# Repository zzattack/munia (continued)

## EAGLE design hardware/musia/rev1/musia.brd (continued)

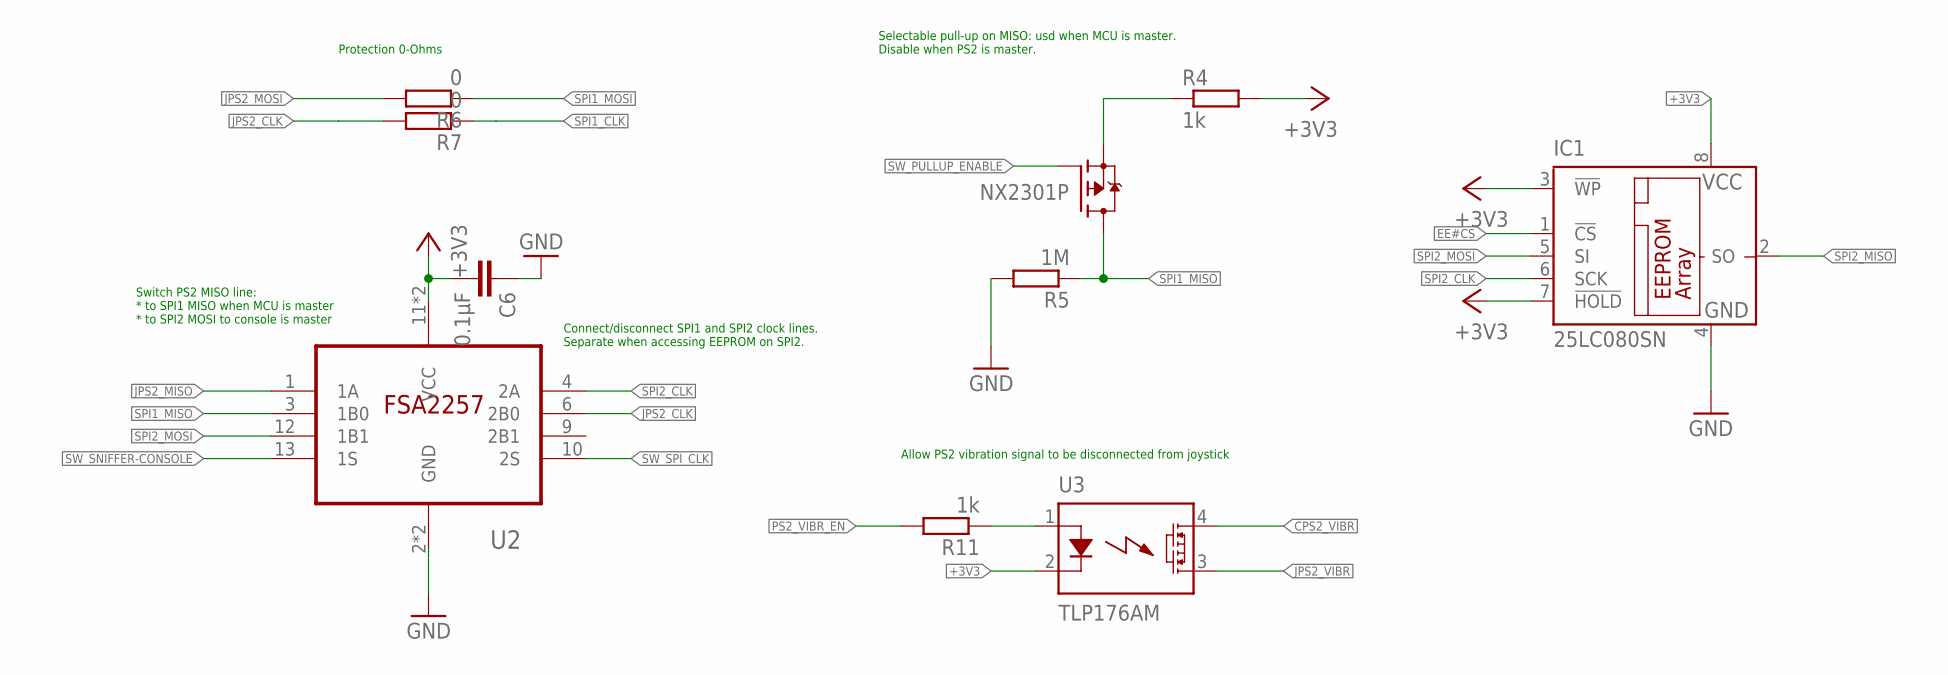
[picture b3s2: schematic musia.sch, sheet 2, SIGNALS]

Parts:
C6: 0.1µF; C0603
IC1: 25LC080SN; SO-08
R4, R11: 1k; R0603
R5: 1M; R0603
R6, R7: 0; R0603
U2: FSA2257; TSSOP14
U3: TLP176AM; SO-6/4
U$3: NX2301P; SOT23

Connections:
+3V3: C6.2, IC1.3 (!WP), IC1.7 (!HOLD), IC1.8 (VCC), R4.2, U2.11 (VCC), U2.14 (VCC), U3.2 (K); also elsewhere on the board
CPS2_VIBR: U3.4 (D1); also elsewhere on the board
EE#CS: IC1.1 (!CS); also elsewhere on the board
GND: C6.1, IC1.4 (GND), R5.2, U2.2 (GND), U2.5 (GND); also elsewhere on the board
JPS2_CLK: R7.2, U2.6 (2B0); also elsewhere on the board
JPS2_MISO: U2.1 (1A); also elsewhere on the board
JPS2_MOSI: R6.2; also elsewhere on the board
JPS2_VIBR: U3.3 (D2); also elsewhere on the board
unnamed: R4.1, U$3.2 (S)
unnamed: R11.1, U3.1 (A)
PS2_VIBR_EN: R11.2; also elsewhere on the board
SPI1_CLK: R7.1; also elsewhere on the board
SPI1_MISO: R5.1, U2.3 (1B0), U$3.3 (D); also elsewhere on the board
SPI1_MOSI: R6.1; also elsewhere on the board
SPI2_CLK: IC1.6 (SCK), U2.4 (2A); also elsewhere on the board
SPI2_MISO: IC1.2 (SO); also elsewhere on the board
SPI2_MOSI: IC1.5 (SI), U2.12 (1B1); also elsewhere on the board
SW_PULLUP_ENABLE: U$3.1 (G); also elsewhere on the board
SW_SNIFFER-CONSOLE: U2.13 (1S); also elsewhere on the board
SW_SPI_CLK: U2.10 (2S); also elsewhere on the board

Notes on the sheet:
Allow PS2 vibration signal to be disconnected from joystick
Selectable pull-up on MISO: usd when MCU is master. Disable when PS2 is master.
Protection 0-Ohms
Switch PS2 MISO line: * to SPI1 MISO when MCU is master * to SPI2 MOSI to console is master
Connect/disconnect SPI1 and SPI2 clock lines. Separate when accessing EEPROM on SPI2.

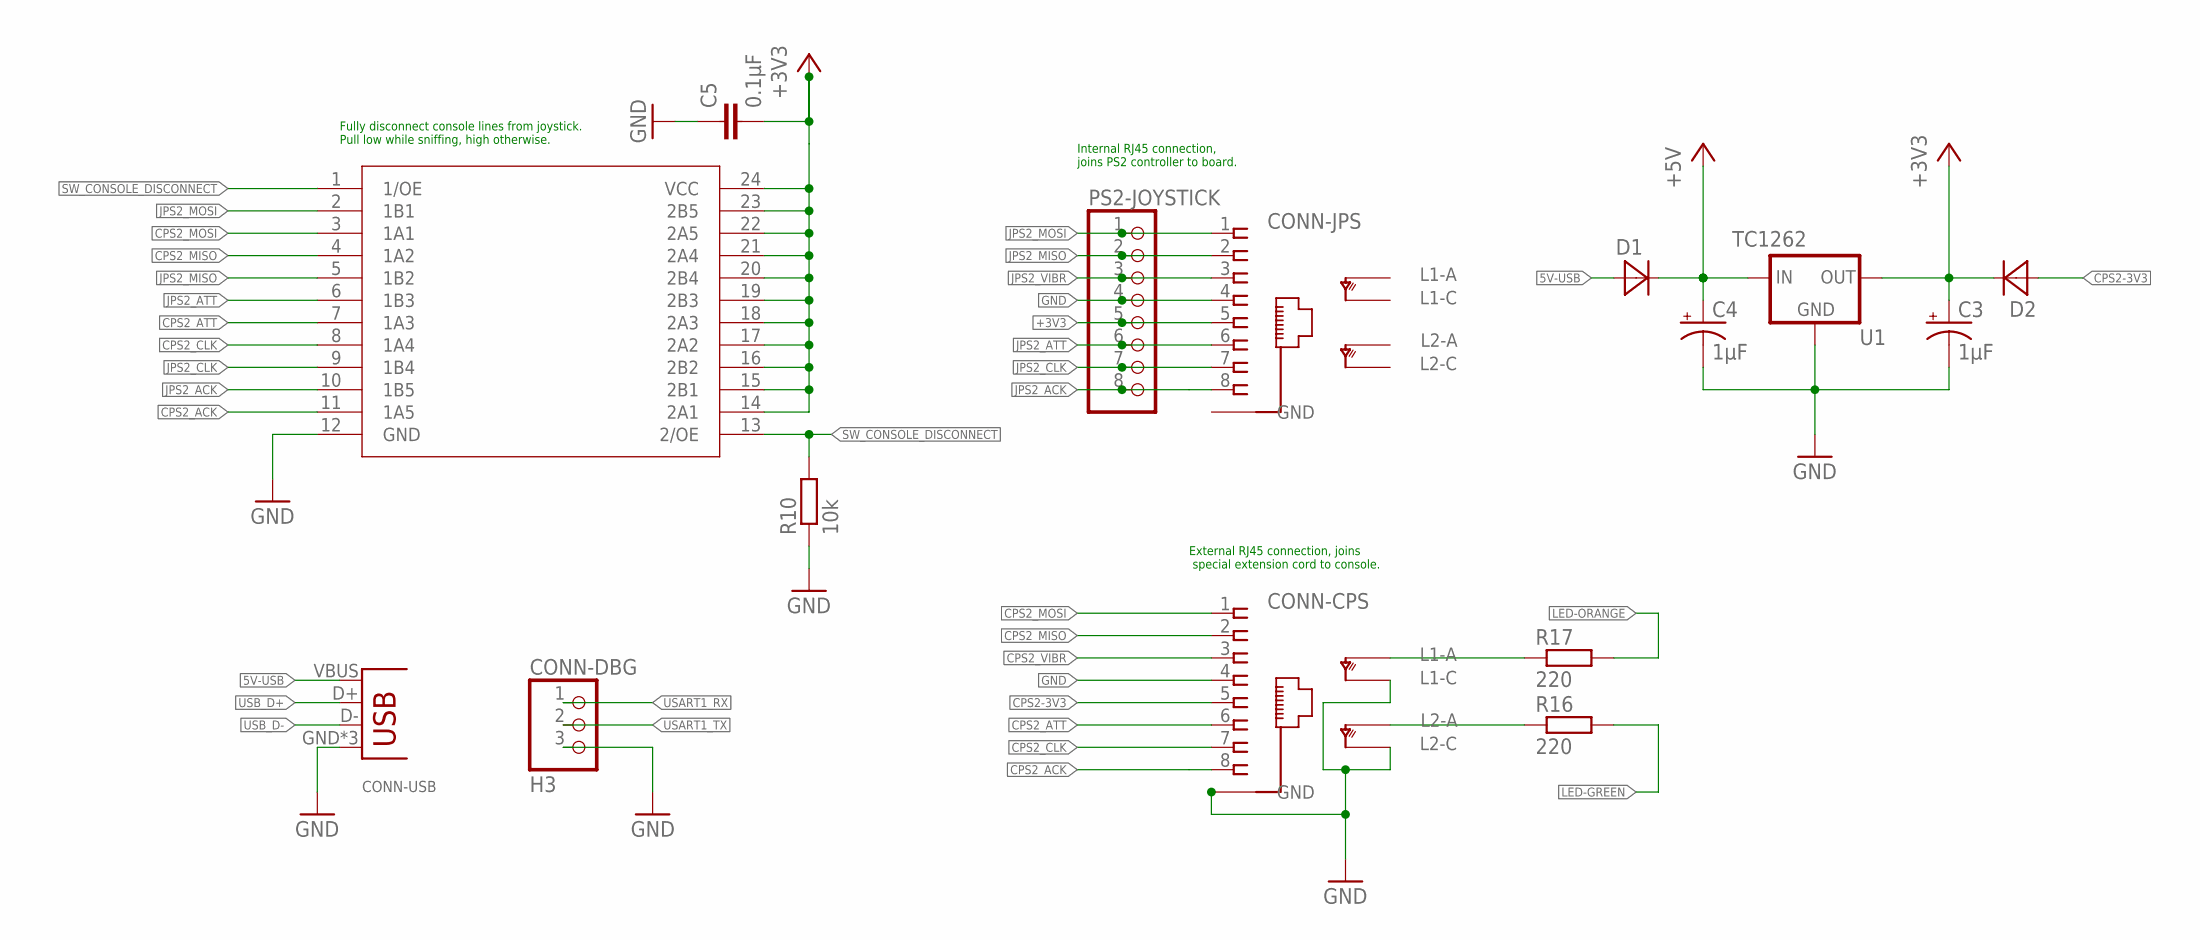
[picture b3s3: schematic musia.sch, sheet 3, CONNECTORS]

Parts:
C3, C4: 1µF; EIA3216
C5: 0.1µF; C0603
CONN-CPS: RJ45-NIELS
CONN-DBG: H3; 1X03
CONN-JPS: RJ45-NIELS
CONN-USB: USB-B-FEMALE; USB-B-H
D1, D2: MBR120VLSFT1G; SOD123
PS2-JOYSTICK: PINHD-1X8; 1X08
R10: 10k; R0603
R16, R17: 220; R0603
U1: TC1262; SOT230P700X180-4N
U$2: SN74CB3Q3384; SSOP24

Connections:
5V-USB: CONN-USB.VBUS, D1.2 (A); also elsewhere on the board
+3V3: C3.A (+), C5.2, CONN-JPS.5, D2.1 (C), PS2-JOYSTICK.5, U1.3 (OUT), U$2.14 (2A1), U$2.15 (2B1), U$2.16 (2B2), U$2.17 (2A2), U$2.18 (2A3), U$2.19 (2B3), U$2.20 (2B4), U$2.21 (2A4), U$2.22 (2A5), U$2.23 (2B5), U$2.24 (VCC); also elsewhere on the board
+5V: C4.A (+), D1.1 (C), U1.1 (IN)
CPS2-3V3: CONN-CPS.5, D2.2 (A)
CPS2_ACK: CONN-CPS.8, U$2.11 (1A5); also elsewhere on the board
CPS2_ATT: CONN-CPS.6, U$2.7 (1A3); also elsewhere on the board
CPS2_CLK: CONN-CPS.7, U$2.8 (1A4); also elsewhere on the board
CPS2_MISO: CONN-CPS.2, U$2.4 (1A2); also elsewhere on the board
CPS2_MOSI: CONN-CPS.1, U$2.3 (1A1); also elsewhere on the board
CPS2_VIBR: CONN-CPS.3; also elsewhere on the board
GND: C3.C (-), C4.C (-), C5.1, CONN-CPS.4, CONN-CPS.GND@5 (GND), CONN-CPS.GND@6 (GND), CONN-CPS.LED-GREEN-C (L2C), CONN-CPS.LED-ORANGE-C (L1C), CONN-DBG.3, CONN-JPS.4, CONN-JPS.GND@5 (GND), CONN-JPS.GND@6 (GND), CONN-USB.GND, CONN-USB.GND@1 (GND), CONN-USB.GND@2 (GND), PS2-JOYSTICK.4, R10.1, U1.2 (GND), U1.4 (GND), U$2.12 (GND); also elsewhere on the board
JPS2_ACK: CONN-JPS.8, PS2-JOYSTICK.8, U$2.10 (1B5); also elsewhere on the board
JPS2_ATT: CONN-JPS.6, PS2-JOYSTICK.6, U$2.6 (1B3); also elsewhere on the board
JPS2_CLK: CONN-JPS.7, PS2-JOYSTICK.7, U$2.9 (1B4); also elsewhere on the board
JPS2_MISO: CONN-JPS.2, PS2-JOYSTICK.2, U$2.5 (1B2); also elsewhere on the board
JPS2_MOSI: CONN-JPS.1, PS2-JOYSTICK.1, U$2.2 (1B1); also elsewhere on the board
JPS2_VIBR: CONN-JPS.3, PS2-JOYSTICK.3; also elsewhere on the board
LED-GREEN: R16.2; also elsewhere on the board
LED-ORANGE: R17.2; also elsewhere on the board
unnamed: CONN-CPS.LED-ORANGE-A (L1A), R17.1
unnamed: CONN-CPS.LED-GREEN-A (L2A), R16.1
SW_CONSOLE_DISCONNECT: R10.2, U$2.1 (1/OE), U$2.13 (2/OE); also elsewhere on the board
USART1_RX: CONN-DBG.1; also elsewhere on the board
USART1_TX: CONN-DBG.2; also elsewhere on the board
USB_D+: CONN-USB.D+; also elsewhere on the board
USB_D-: CONN-USB.D-; also elsewhere on the board

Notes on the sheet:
Fully disconnect console lines from joystick. Pull low while sniffing, high otherwise.
External RJ45 connection, joins special extension cord to console.
Internal RJ45 connection, joins PS2 controller to board.

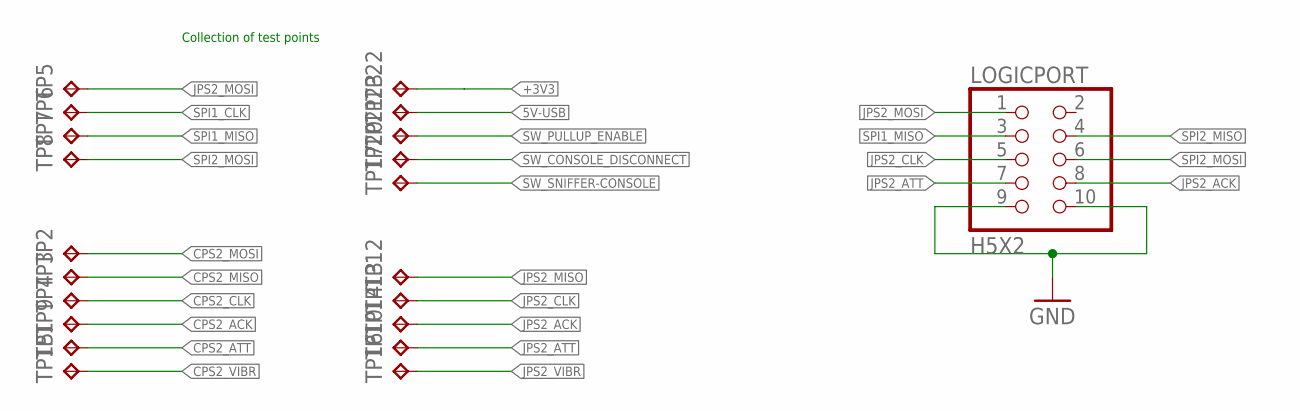
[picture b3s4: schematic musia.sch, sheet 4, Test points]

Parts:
LOGICPORT: H5X2; 2X05
TP1, TP2, TP3, TP4, TP5, TP6, TP7, TP8, TP9, TP10, TP12, TP13, TP14, TP15, TP16, TP17, TP20, TP21, TP22, TP23: TPB1,27; B1,27

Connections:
5V-USB: TP23.TP; also elsewhere on the board
+3V3: TP22.TP; also elsewhere on the board
CPS2_ACK: TP9.TP; also elsewhere on the board
CPS2_ATT: TP1.TP; also elsewhere on the board
CPS2_CLK: TP4.TP; also elsewhere on the board
CPS2_MISO: TP3.TP; also elsewhere on the board
CPS2_MOSI: TP2.TP; also elsewhere on the board
CPS2_VIBR: TP15.TP; also elsewhere on the board
GND: LOGICPORT.9, LOGICPORT.10; also elsewhere on the board
JPS2_ACK: LOGICPORT.8, TP14.TP; also elsewhere on the board
JPS2_ATT: LOGICPORT.7, TP10.TP; also elsewhere on the board
JPS2_CLK: LOGICPORT.5, TP13.TP; also elsewhere on the board
JPS2_MISO: TP12.TP; also elsewhere on the board
JPS2_MOSI: LOGICPORT.1, TP5.TP; also elsewhere on the board
JPS2_VIBR: TP16.TP; also elsewhere on the board
SPI1_CLK: TP6.TP; also elsewhere on the board
SPI1_MISO: LOGICPORT.3, TP7.TP; also elsewhere on the board
SPI2_MISO: LOGICPORT.4; also elsewhere on the board
SPI2_MOSI: LOGICPORT.6, TP8.TP; also elsewhere on the board
SW_CONSOLE_DISCONNECT: TP20.TP; also elsewhere on the board
SW_PULLUP_ENABLE: TP21.TP; also elsewhere on the board
SW_SNIFFER-CONSOLE: TP17.TP; also elsewhere on the board

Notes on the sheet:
Collection of test points

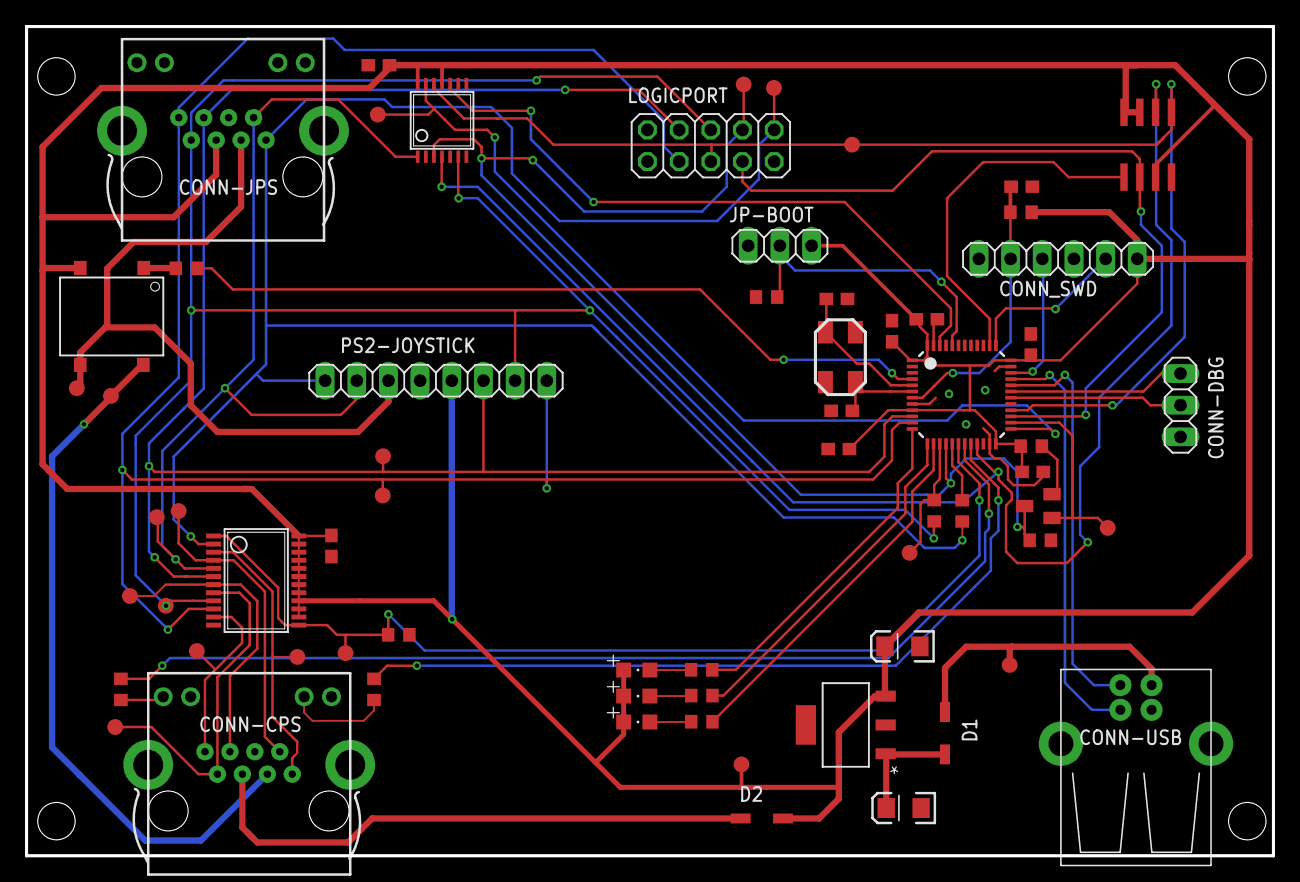
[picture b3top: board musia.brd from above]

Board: 2 copper layers, 100.0 x 66.5 mm, 66 parts (0 on the bottom side), 51 nets.
